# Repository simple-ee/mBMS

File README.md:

# WARNING!
Just a reminder that this is a DIY product/solution so don’t use this for safety 
critical systems or in any situation where there could be a risk to life. 
There is no warranty, it may not work as expected or at all.

# modular BMS by simple-ee.com
This is what I am calling the modular BMS for an 8S LiFePO4 pack.  I've designed
this as three main parts.  Currently this design is functional and running my
system but I am in the progress of overhauling the design by upgrading from an 
8-bit ATmega328PB to a 32-bit SAMD21G18 using the arduino zero bootloader.

Right now I'm essentially maxed out resources and memory on the atmega328PB and
cannot add anymore features which is why I'm planning on upgrading the design.

Even though this design is now my old design its still very functional and very
stable as it has been running my 4kWh system for about 6 months and protecting 
the cells perfectly.  

The reason for making it a modular design is for easy upgradability and also,
considering the current chip shortage, is to replace sections of the board in
case there are no parts available.  This will prevent the need to redo and 
re-layout of the entire design.

I'm posting this design because I've learned a lot from other projects and feel
this will help a lot of people and want to give back.  Also smarter people than
me could take this design and help optomize the code and design and make this a
community BMS.

## the Table of Contents
1. [the Setup](#thesetup)
    1. [Software/Bootloader](#software)
    2. [Wiring and Connection](#connect)
2. [Pinout and Block Diagram](#pinout)
3. [Board Information](#information)
    1. [the Protection Board](#theProtectionBoard)
    2. [the BMS Board](#theBMSBoard)
    3. [the Passive Board](#thePassiveBoard)
    4. [the Display](#display)

## the SETUP 

### Software/Bootloader 
[Software Setup](https://github.com/simple-ee/mBMS/tree/main/Setup)

### Wiring and Connection 
#### Single 8S Pack Wiring Diagram
Here we have the wiring diagram for connecting the mBMS to an 8S pack and is considered a single pack system:

#### Parallel multiple 8S Wiring Diagram
Here we have the wiring diagram for connecting multiple 8S packs in parallel.  Here each 8S pack is protected by its own mBMS and then they are paralleled together using 
ideal diodes to make sure that the other packs in parallel do not charge or discharge a pack that has gone into protection.  I designed the system this way to allow
for scalability of system storage.  By protecting each pack separately then you can, theoretically, add tens of hundreds of 8S packs in parallel when you need more storage
without having to reconfigure your system to add more storage or turn off the system to add more storage.

## Pinout and Block Diagram 

### the Protection Board

## Board information 

### the Protection board 

[kicad Files and gerber files](https://github.com/simple-ee/mBMS/tree/main/Schematic/The%20Protection%20Board)

#### Rendered PCB

#### Actual PCB

- This board will handle discharge and charge currents between the battery
and the external world.  
- It has the following specs:

    Item | Description
    -----|------------
    1 | 4-Channel 16-BIT ADC with an effective resolution of 16-Bit at 20sps
    2 | 100A hall effect current sensor
    3 | Up to 3 Discharge N-Channel MOSFETS with 0.7mOhm DCR and 425A current capability. ( Effective current handling per mosfet without heatsink is 30A)
    4 | Up to 2 charge N-Channle MOSFETS with 0.7mOhm DCR and 425A current capability. (Effective current handling per mosfet without heatsink is 30A)
    5 | Optoisolator to drive the charge mosfets as it is floating relative to the battery ground.
    6 | High efficiency buck converter to power the MCU and supporting circuits.
    7 | Low power LDO to power the secondary side of the optoisolator to drive the charge MOSFET
    8 | Two I2C ports, one to act as an internal COM for adc and display, andsecond one to act as external COM to relay information to BMS board
    9 | 125A fuse that will act as the short circuit protection with a breaking capacity of 1kA.

### the BMS Board 

[kicad Files and gerber files](https://github.com/simple-ee/mBMS/tree/main/Schematic/The%20BMS%20Board)

#### Rendered PCB

#### Actual PCB

- This board is handling the cell level monitoring function as well as sending
controls to the passive balance resistors for balancing the cells.  It 
incorporates cell level OVP and UVP which is configurable and also receives the
current values from the Protection board via I2C and then displays all values
on a TFT display either ST7735 or ST7789.  If for any reason a fault is triggered
or one of the configured protection values is triggered you can send a reset
fault command either via an external trigger button or serial command over uart.
- It has the following specs:

Item | Description
-----|------------
1 | x2 4-Channel 16-BIT ADC with an effective resolution of 16-BIT at 20sps
2 | External 16MHz Crystal oscillator
3 | External SPI port to connect TFT display
4 | Can be powered via the battery pack or external power source
5 | External action button. Default state is for reset fault condition

### the Passive Balance Board 

[kicad Files and gerber files](https://github.com/simple-ee/mBMS/tree/main/Schematic/The%20Passive%20Balance%20Board)

#### Rendered PCB

#### Actual PCB

The passive board essentially is controlled by the BMS board to allow the 
bleeder resistor to slow down the rate of charge for that particular cell when
the BMS board detects that the cell is too high of a delta from the rest.

Currently I have a 2W 10R resistor but I'm having thermal issues because its 
quite a lot of power to dissapate over the whole board so I'd recommend a 22R 2W
resistor which is still good for what you need but will not cause any potential
damage.

The board also have the option of adding thermal jumpers and if you do decide to 
do that then I'd recommend a 2oz copper for that PCB.  Thermal jumpers are electrically
isolated and allow you to connect directly to ground without shorting anything
which is pretty awesome in my opinion.

Heres the link for the thermal jumpers.  They are really awesome but with the chip
shortage its a decent lead time for them.

https://www.digikey.com/en/products/detail/vishay-dale-thin-film/THJP0612AST1/11313314

### the Display (optional) 

Currently the SoC is not an implemented function its just a placeholder.  But if
anyone is willing to help out with this SoC code section then that would be 
awesome as I'm still not sure the best way to implement this.

The screen is to be used with the BMS board.  the Protection does not have 
the ability to use a SPI TFT display but if you use it on its own, then you can
add an I2C oled display because the secondary I2C will not be used.

Here is a link to the tft display that I used.
https://www.adafruit.com/product/4383

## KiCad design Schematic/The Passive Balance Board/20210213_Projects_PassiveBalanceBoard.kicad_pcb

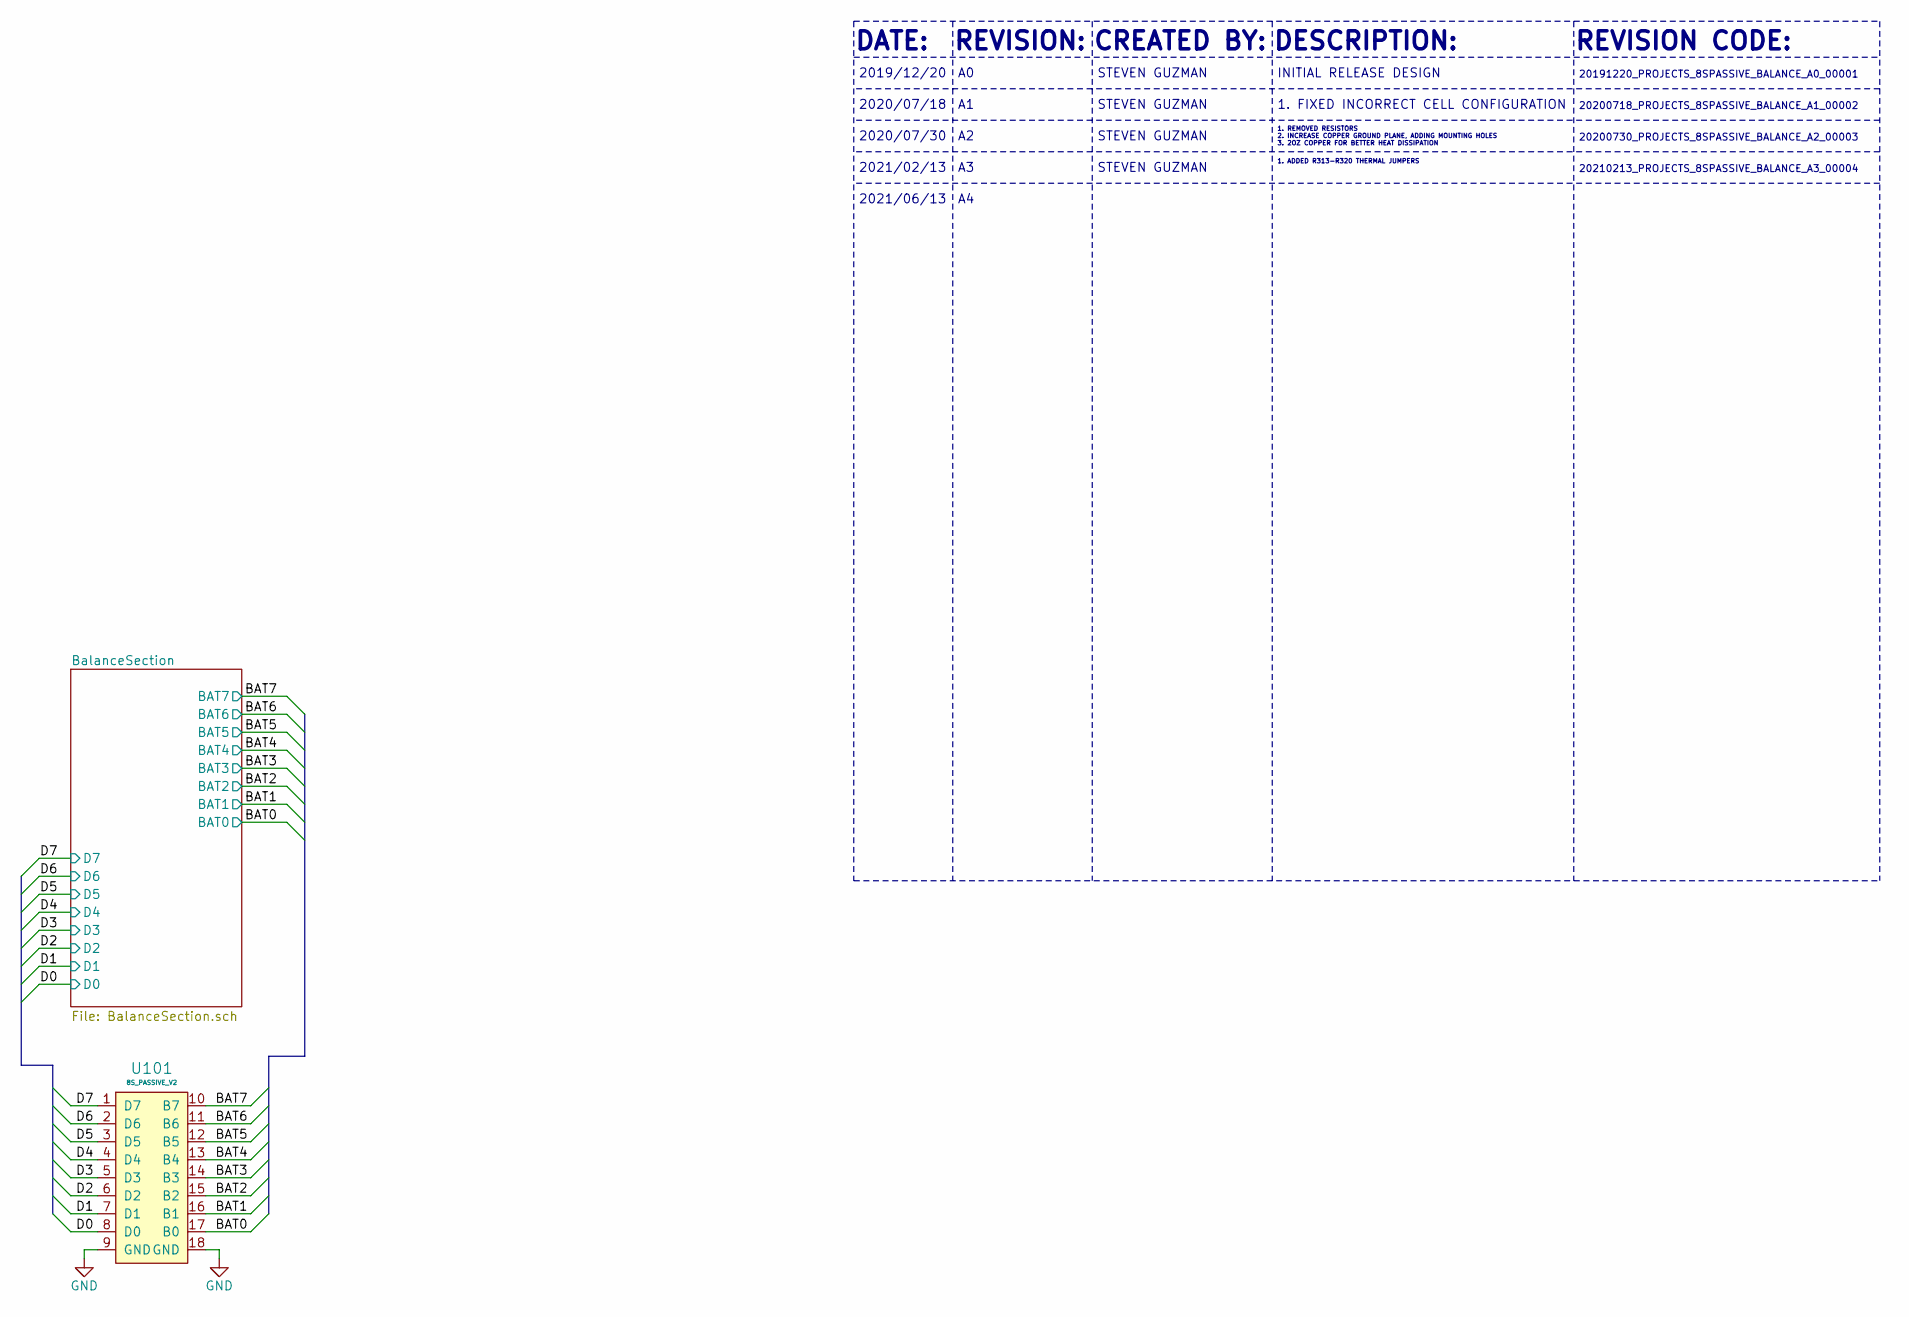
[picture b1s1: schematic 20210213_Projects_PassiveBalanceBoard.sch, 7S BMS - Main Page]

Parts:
U101: 8S_PASSIVE_V2

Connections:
/BAT0: U101.17 (B0); also elsewhere on the board
/BAT1: U101.16 (B1); also elsewhere on the board
/BAT2: U101.15 (B2); also elsewhere on the board
/BAT3: U101.14 (B3); also elsewhere on the board
/BAT4: U101.13 (B4); also elsewhere on the board
/BAT5: U101.12 (B5); also elsewhere on the board
/BAT6: U101.11 (B6); also elsewhere on the board
/BAT7: U101.10 (B7); also elsewhere on the board
/D0: U101.8 (D0); also elsewhere on the board
/D1: U101.7 (D1); also elsewhere on the board
/D2: U101.6 (D2); also elsewhere on the board
/D3: U101.5 (D3); also elsewhere on the board
/D4: U101.4 (D4); also elsewhere on the board
/D5: U101.3 (D5); also elsewhere on the board
/D6: U101.2 (D6); also elsewhere on the board
/D7: U101.1 (D7); also elsewhere on the board
GND: U101.9 (GND), U101.18 (GND); also elsewhere on the board

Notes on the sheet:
DATE:
DESCRIPTION:
REVISION:
REVISION CODE:
2019/12/20
CREATED BY:
STEVEN GUZMAN
INITIAL RELEASE DESIGN
20191220_PROJECTS_8SPASSIVE_BALANCE_A0_00001
2020/07/18
1. FIXED INCORRECT CELL CONFIGURATION
20200718_PROJECTS_8SPASSIVE_BALANCE_A1_00002
2020/07/30
1. REMOVED RESISTORS 2. INCREASE COPPER GROUND PLANE, ADDING MOUNTING HOLES 3. 2OZ COPPER FOR BETTER HEAT DISSIPATION
20200730_PROJECTS_8SPASSIVE_BALANCE_A2_00003
2021/02/13
1. ADDED R313-R320 THERMAL JUMPERS
20210213_PROJECTS_8SPASSIVE_BALANCE_A3_00004
2021/06/13

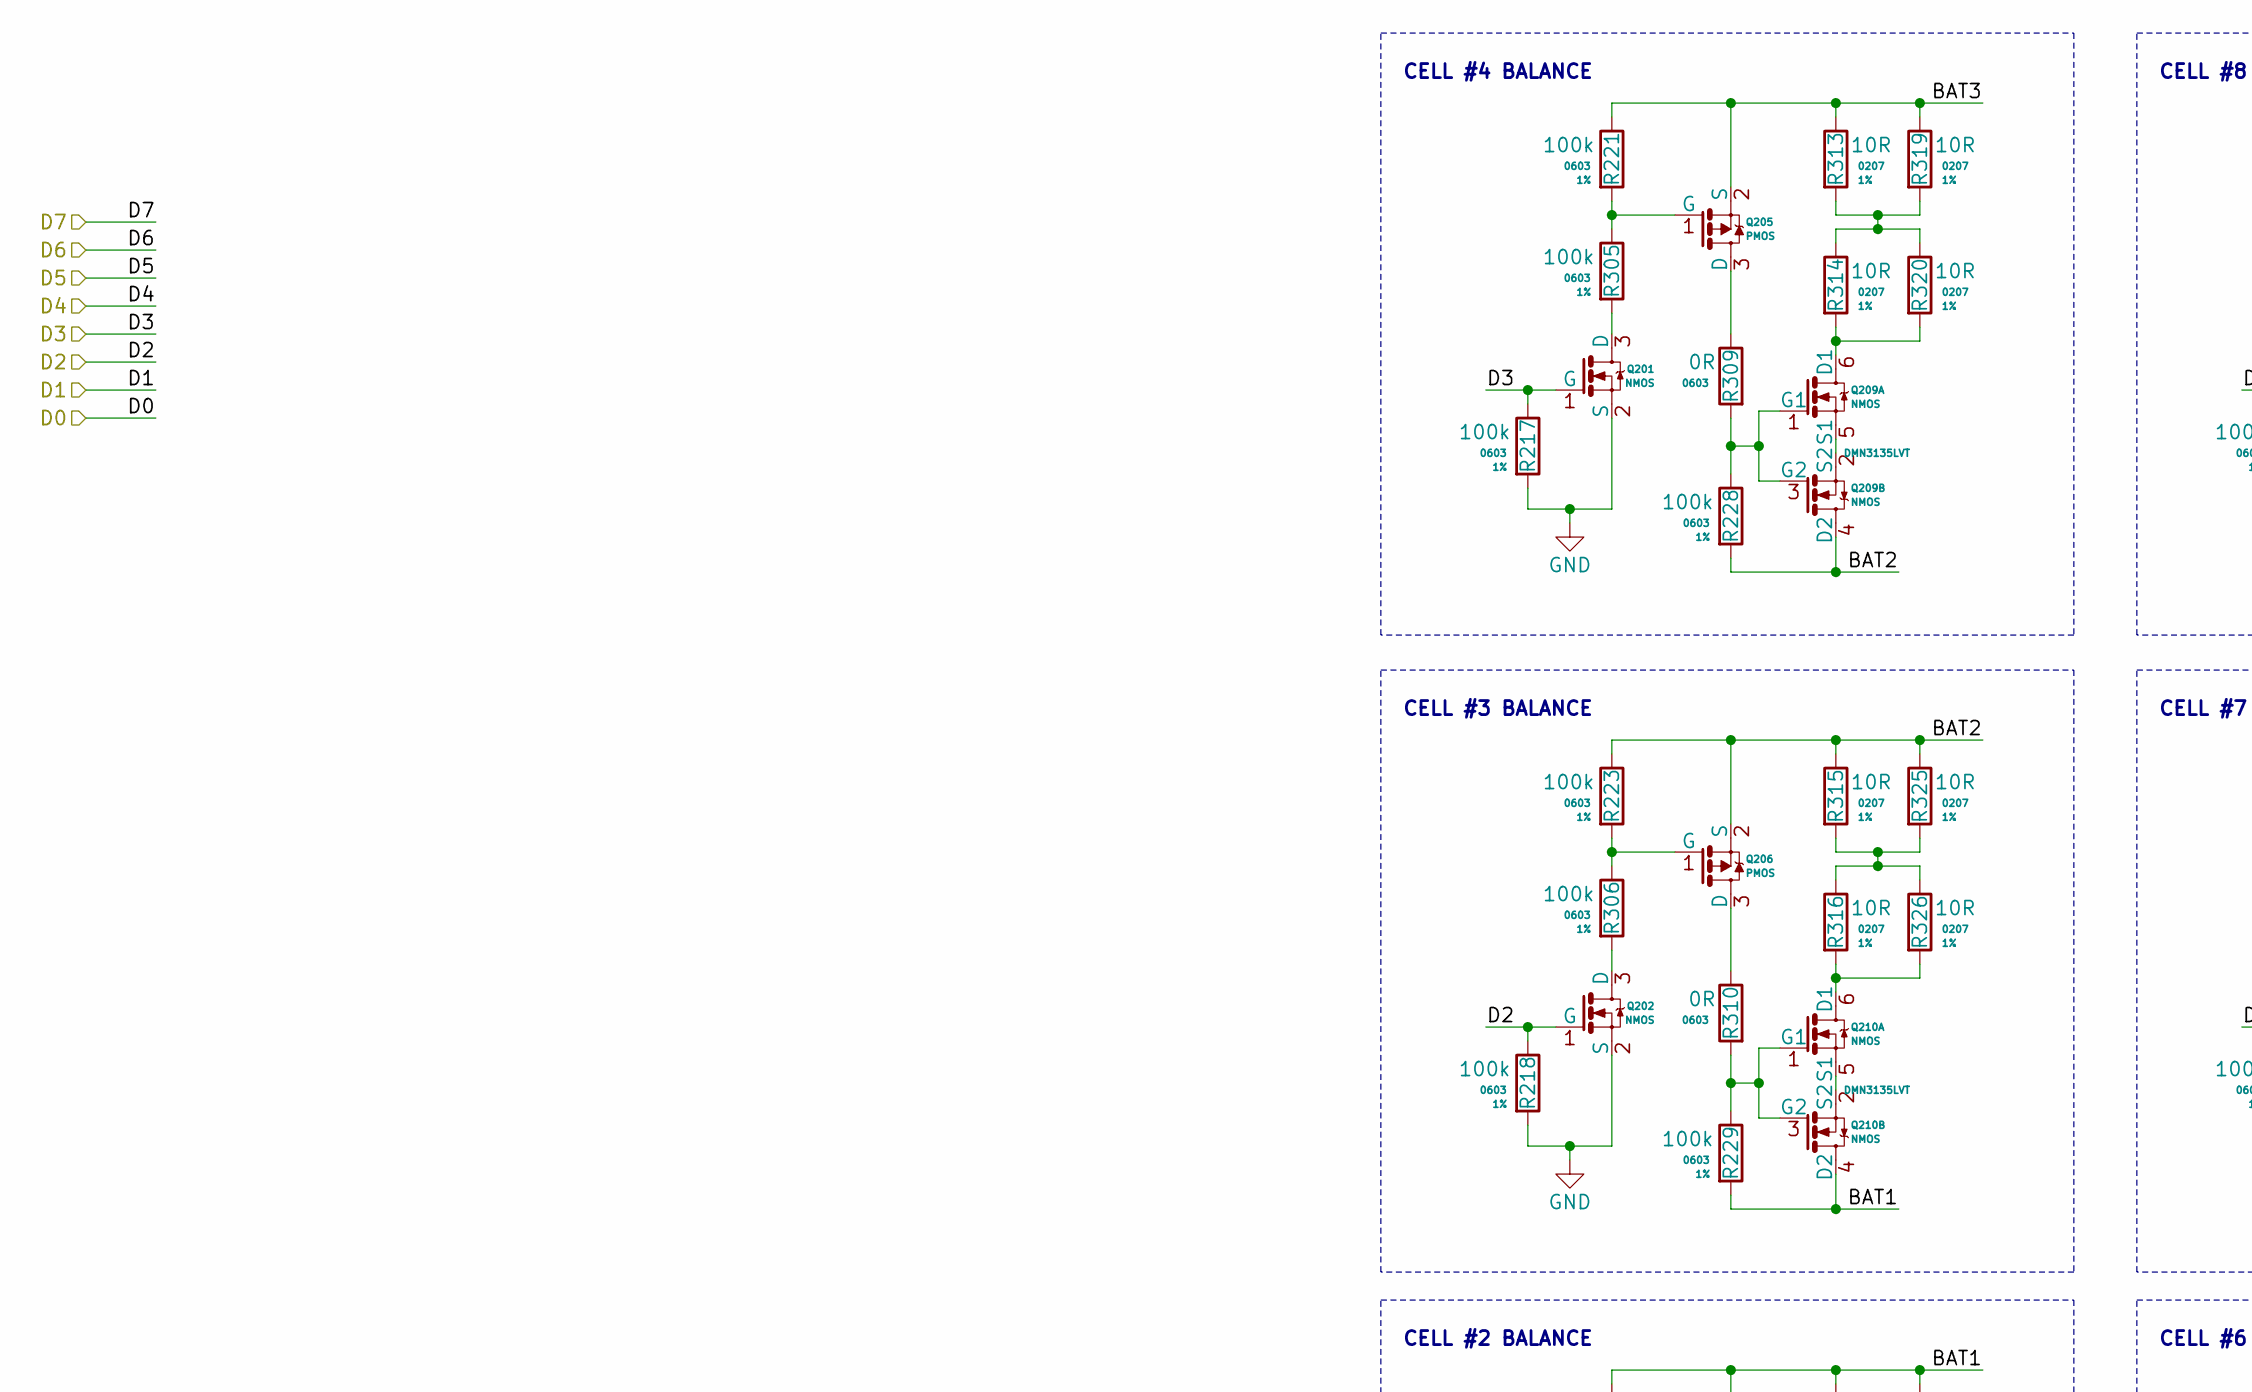
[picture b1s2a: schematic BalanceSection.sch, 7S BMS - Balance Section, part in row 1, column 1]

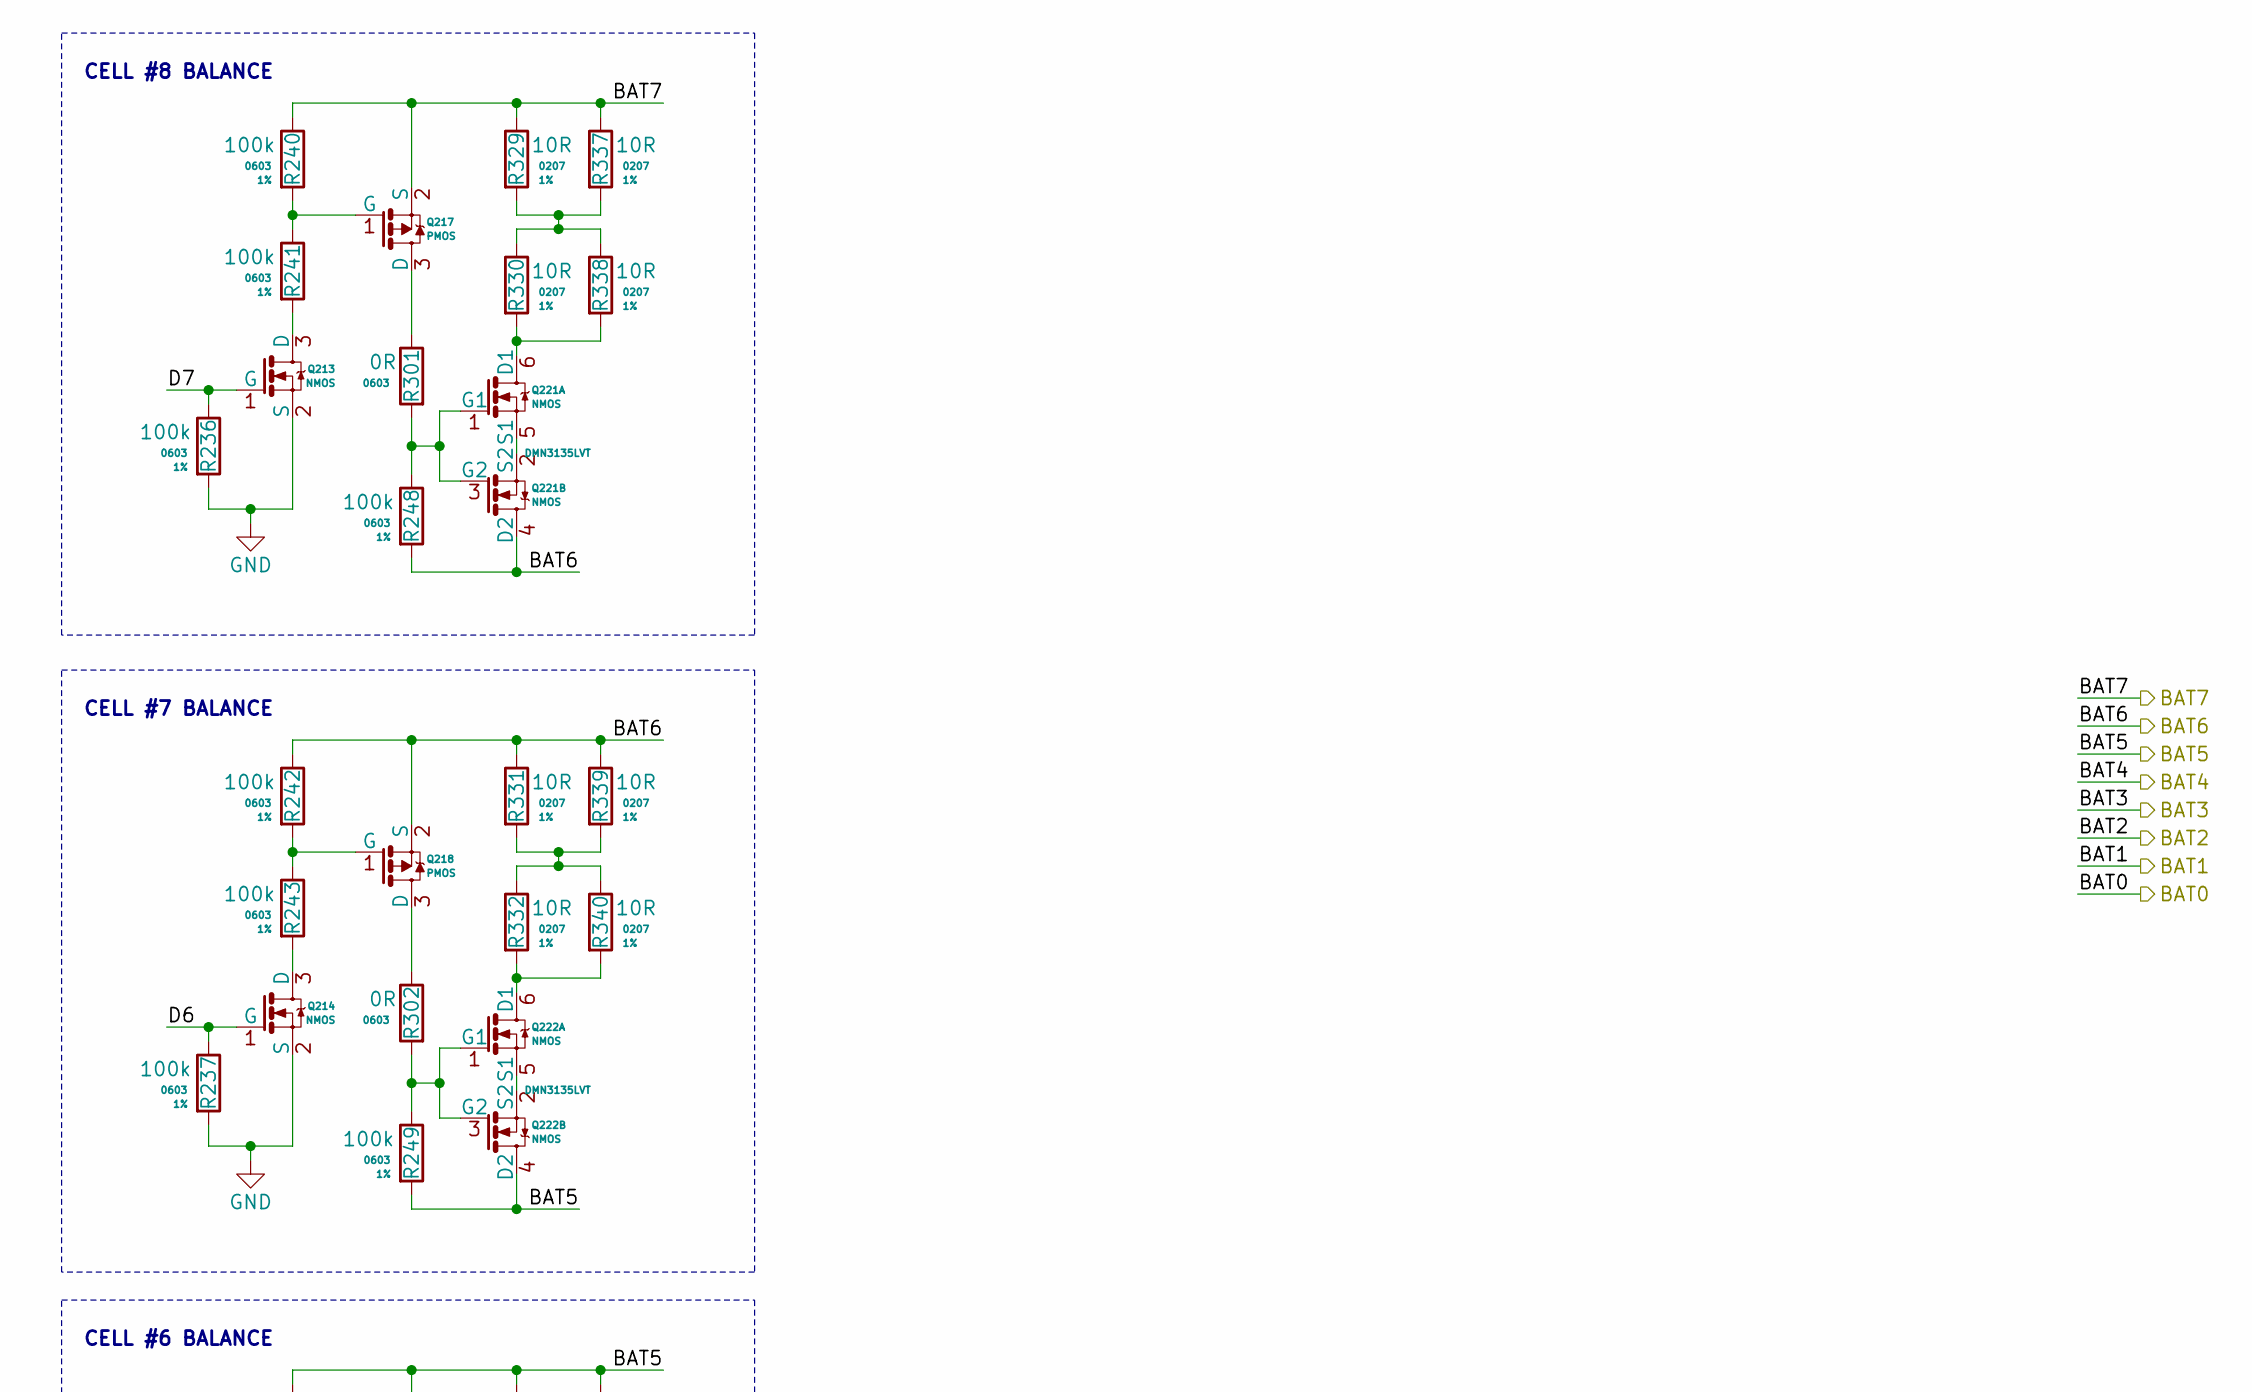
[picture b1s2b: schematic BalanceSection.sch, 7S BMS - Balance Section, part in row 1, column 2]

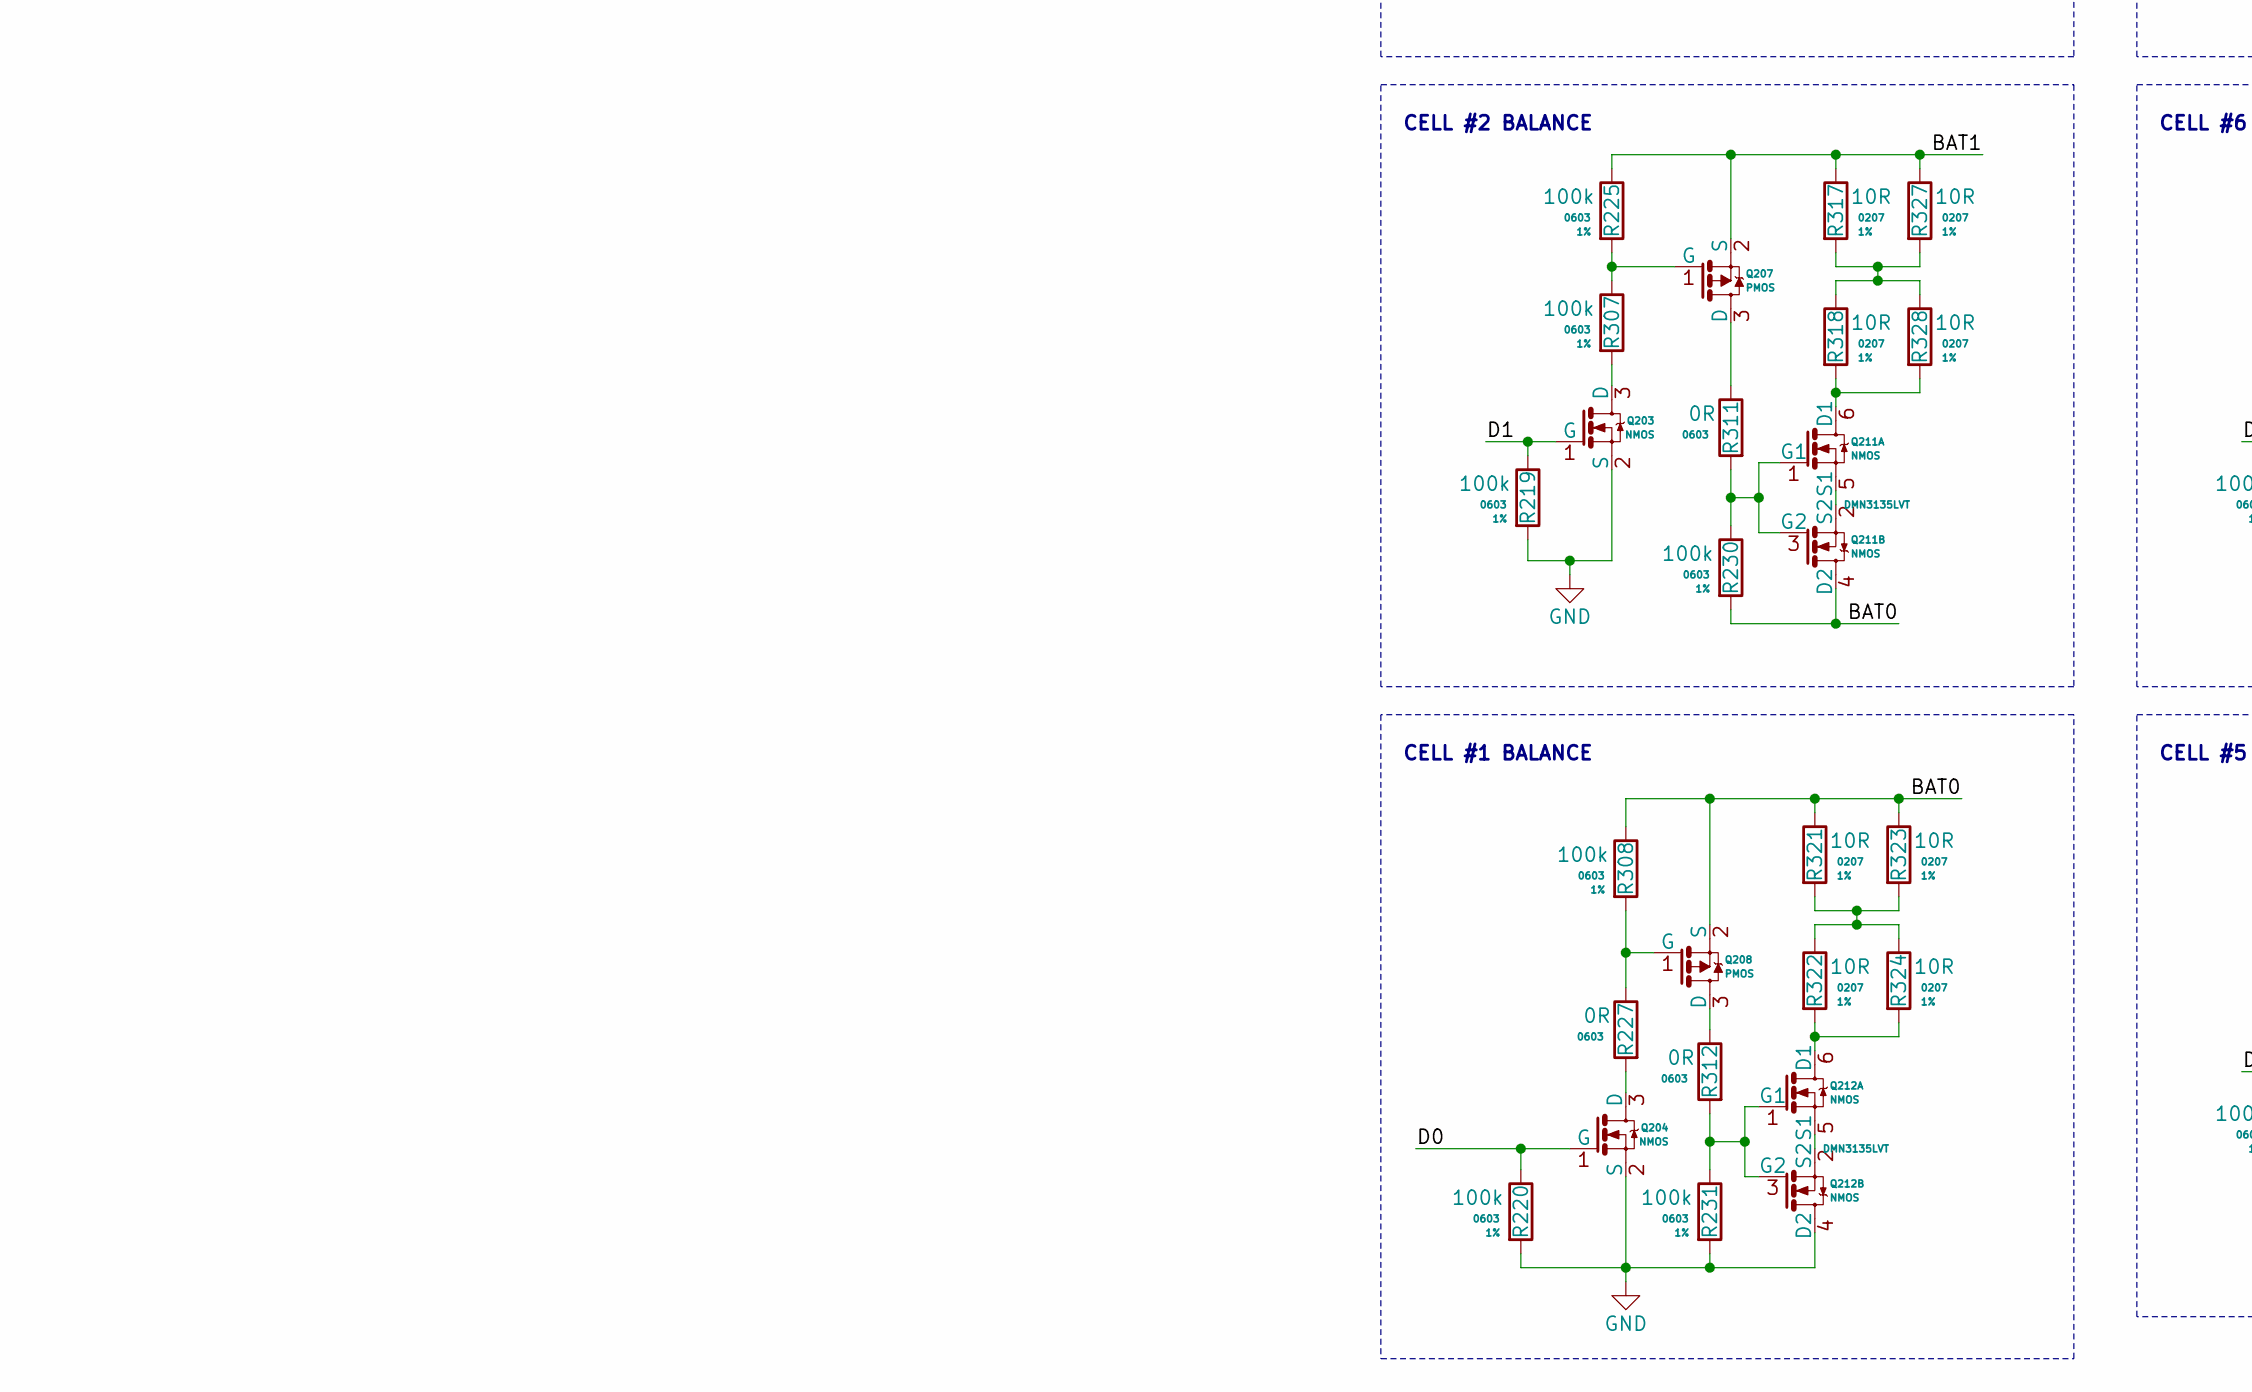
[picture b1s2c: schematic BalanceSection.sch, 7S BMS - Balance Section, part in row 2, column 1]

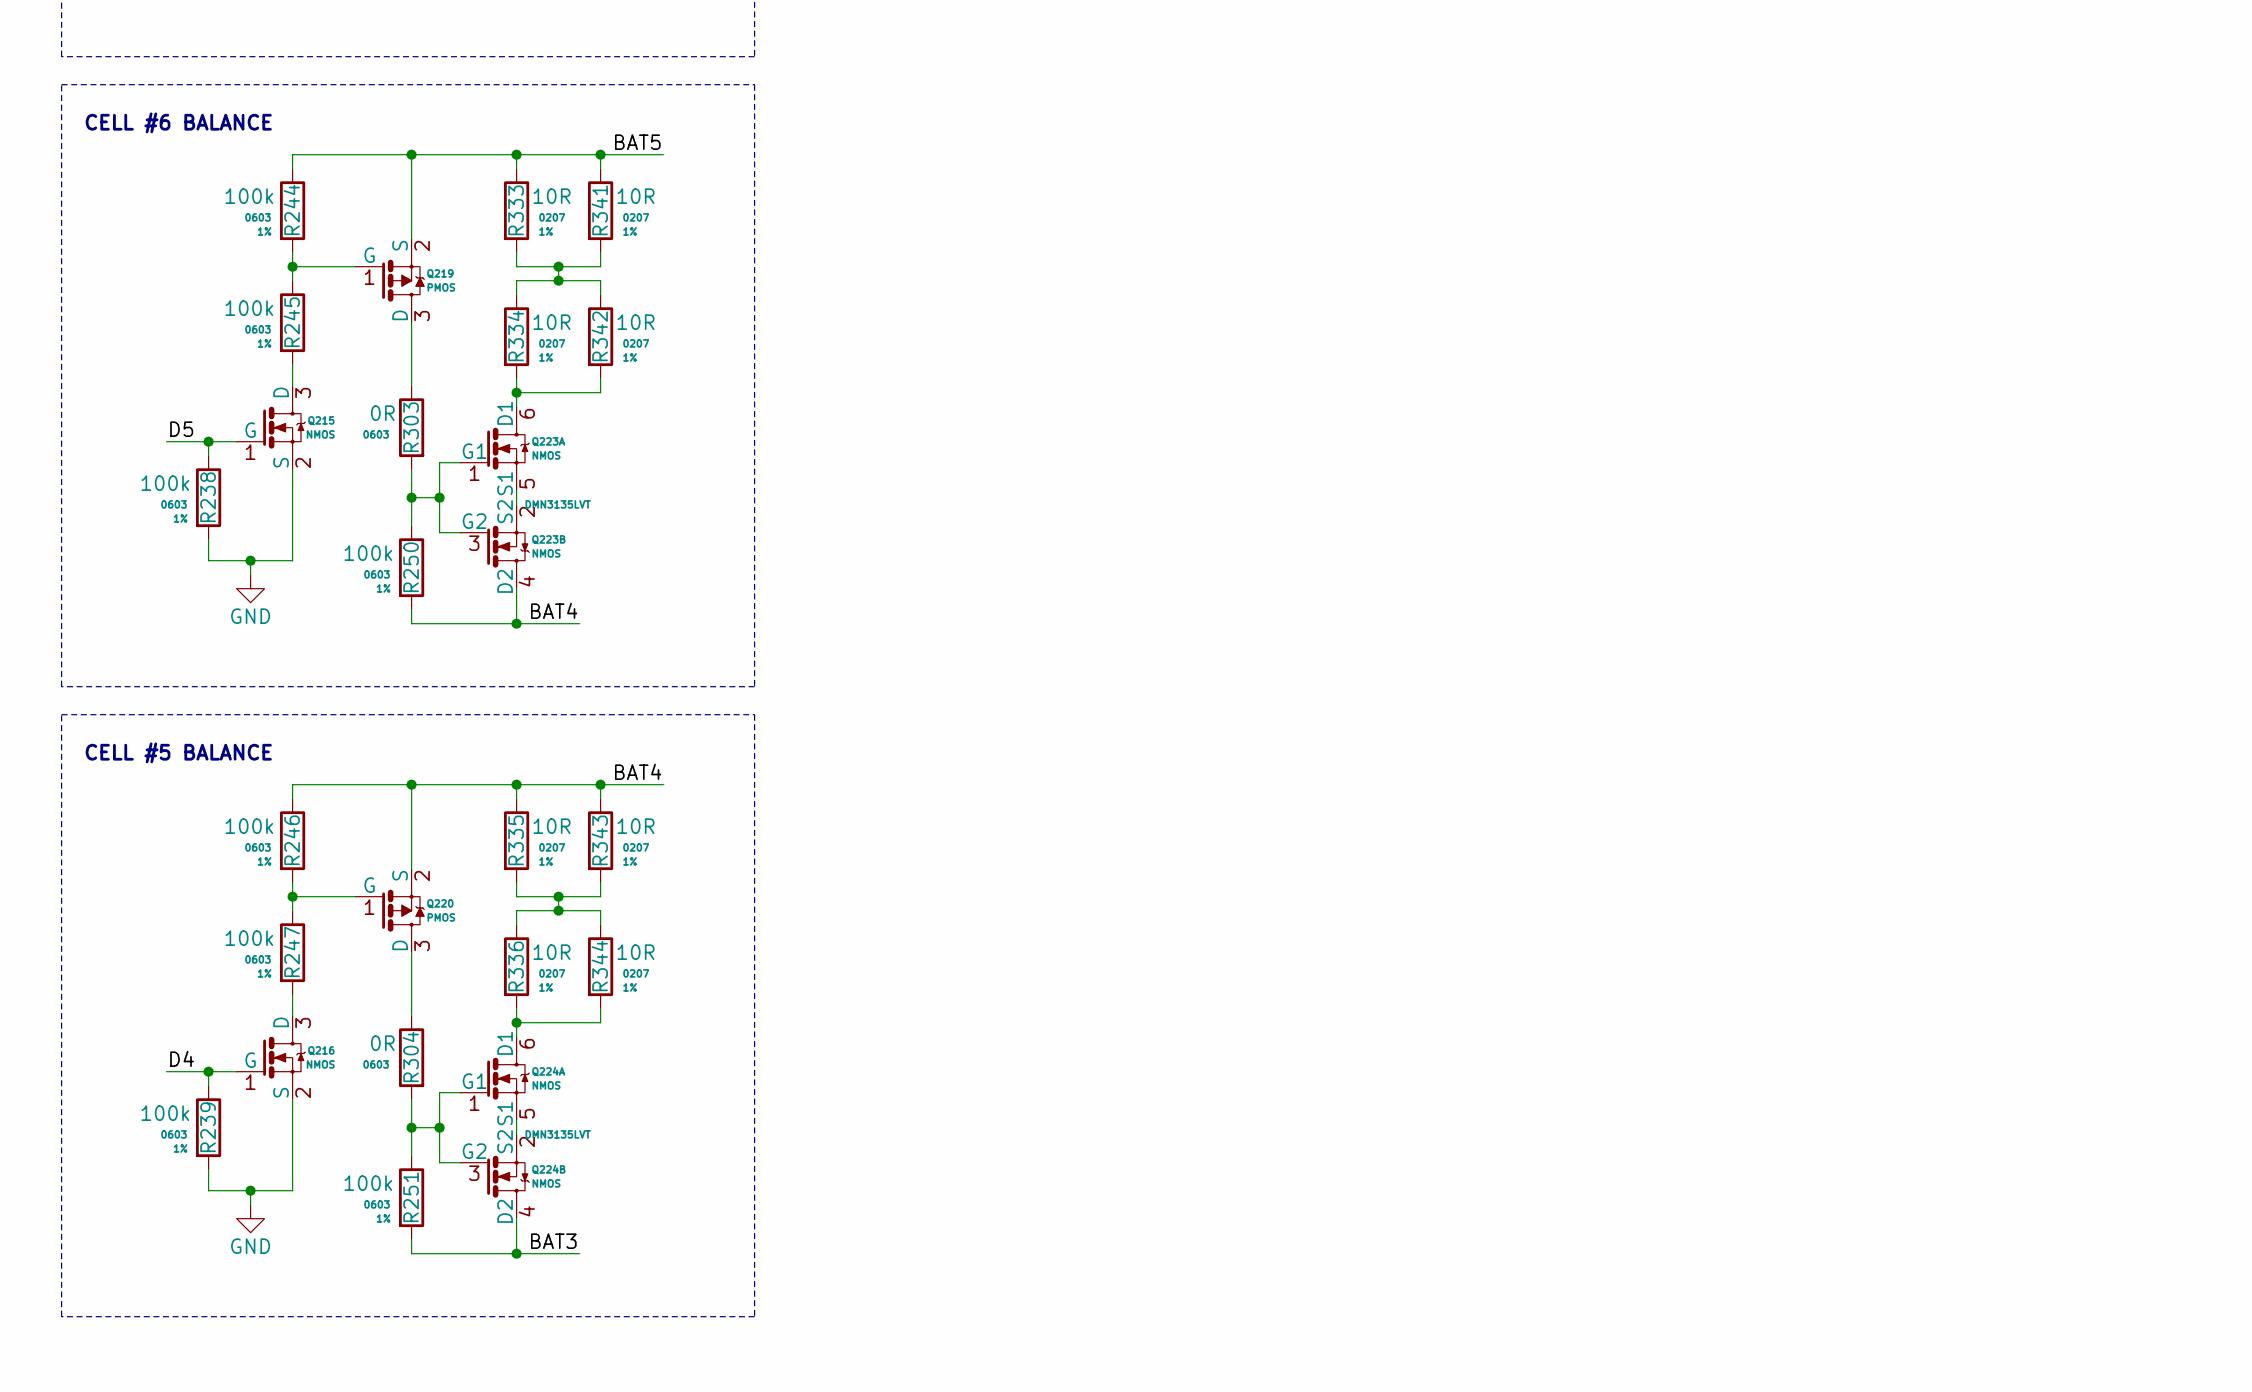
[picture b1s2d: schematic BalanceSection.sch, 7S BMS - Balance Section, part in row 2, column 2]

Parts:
Q201, Q202, Q203, Q204, Q213, Q214, Q215, Q216: 2N7002-7-F; SOT-23-3
Q205, Q206, Q207, Q208, Q217, Q218, Q219, Q220: BSS84LT1G; SOT-23-3
Q209, Q210, Q211, Q212, Q221, Q222, Q223, Q224: DMN3135LVT; SOT-23-6
R217, R218, R219, R220, R221, R223, R225, R228, R229, R230, R231, R236, R237, R238, R239, R240, R241, R242, R243, R244, R245, R246, R247, R248, R249, R250, R251, R305, R306, R307, R308: CPF0603F100KC1; R_0603_Handsolder
R227, R301, R302, R303, R304, R309, R310, R311, R312: RMCF0603ZT0R00; R_0603_Handsolder
R313, R314, R315, R316, R317, R318, R319, R320, R321, R322, R323, R324, R325, R326, R327, R328, R329, R330, R331, R332, R333, R334, R335, R336, R337, R338, R339, R340, R341, R342, R343, R344: MLFA1FTC10R0; R_MELF_0207

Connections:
/BAT0: Q208.2 (S), Q211.4 (D2), R230.2, R308.1, R321.1, R323.1; also elsewhere on the board
/BAT1: Q207.2 (S), Q210.4 (D2), R225.1, R229.2, R317.1, R327.1; also elsewhere on the board
/BAT2: Q206.2 (S), Q209.4 (D2), R223.1, R228.2, R315.1, R325.1; also elsewhere on the board
/BAT3: Q205.2 (S), Q224.4 (D2), R221.1, R251.2, R313.1, R319.1; also elsewhere on the board
/BAT4: Q220.2 (S), Q223.4 (D2), R246.1, R250.2, R335.1, R343.1; also elsewhere on the board
/BAT5: Q219.2 (S), Q222.4 (D2), R244.1, R249.2, R333.1, R341.1; also elsewhere on the board
/BAT6: Q218.2 (S), Q221.4 (D2), R242.1, R248.2, R331.1, R339.1; also elsewhere on the board
/BAT7: Q217.2 (S), R240.1, R329.1, R337.1; also elsewhere on the board
/D0: Q204.1 (G), R220.1; also elsewhere on the board
/D1: Q203.1 (G), R219.1; also elsewhere on the board
/D2: Q202.1 (G), R218.1; also elsewhere on the board
/D3: Q201.1 (G), R217.1; also elsewhere on the board
/D4: Q216.1 (G), R239.1; also elsewhere on the board
/D5: Q215.1 (G), R238.1; also elsewhere on the board
/D6: Q214.1 (G), R237.1; also elsewhere on the board
/D7: Q213.1 (G), R236.1; also elsewhere on the board
GND: Q201.2 (S), Q202.2 (S), Q203.2 (S), Q204.2 (S), Q212.4 (D2), Q213.2 (S), Q214.2 (S), Q215.2 (S), Q216.2 (S), R217.2, R218.2, R219.2, R220.2, R231.2, R236.2, R237.2, R238.2, R239.2; also elsewhere on the board
unnamed: Q201.3 (D), R305.2
unnamed: Q202.3 (D), R306.2
unnamed: Q203.3 (D), R307.2
unnamed: Q204.3 (D), R227.2
unnamed: Q205.1 (G), R221.2, R305.1
unnamed: Q205.3 (D), R309.1
unnamed: Q206.1 (G), R223.2, R306.1
unnamed: Q206.3 (D), R310.1
unnamed: Q207.1 (G), R225.2, R307.1
unnamed: Q207.3 (D), R311.1
unnamed: Q208.1 (G), R227.1, R308.2
unnamed: Q208.3 (D), R312.1
unnamed: Q209.1 (G1), Q209.3 (G2), R228.1, R309.2
unnamed: Q209.2 (S2), Q209.5 (S1)
unnamed: Q209.6 (D1), R314.2, R320.2
unnamed: Q210.1 (G1), Q210.3 (G2), R229.1, R310.2
unnamed: Q210.2 (S2), Q210.5 (S1)
unnamed: Q210.6 (D1), R316.2, R326.2
unnamed: Q211.1 (G1), Q211.3 (G2), R230.1, R311.2
unnamed: Q211.2 (S2), Q211.5 (S1)
unnamed: Q211.6 (D1), R318.2, R328.2
unnamed: Q212.1 (G1), Q212.3 (G2), R231.1, R312.2
unnamed: Q212.2 (S2), Q212.5 (S1)
unnamed: Q212.6 (D1), R322.2, R324.2
unnamed: Q213.3 (D), R241.2
unnamed: Q214.3 (D), R243.2
unnamed: Q215.3 (D), R245.2
unnamed: Q216.3 (D), R247.2
unnamed: Q217.1 (G), R240.2, R241.1
unnamed: Q217.3 (D), R301.1
unnamed: Q218.1 (G), R242.2, R243.1
unnamed: Q218.3 (D), R302.1
unnamed: Q219.1 (G), R244.2, R245.1
unnamed: Q219.3 (D), R303.1
unnamed: Q220.1 (G), R246.2, R247.1
unnamed: Q220.3 (D), R304.1
unnamed: Q221.1 (G1), Q221.3 (G2), R248.1, R301.2
unnamed: Q221.2 (S2), Q221.5 (S1)
unnamed: Q221.6 (D1), R330.2, R338.2
unnamed: Q222.1 (G1), Q222.3 (G2), R249.1, R302.2
unnamed: Q222.2 (S2), Q222.5 (S1)
unnamed: Q222.6 (D1), R332.2, R340.2
unnamed: Q223.1 (G1), Q223.3 (G2), R250.1, R303.2
unnamed: Q223.2 (S2), Q223.5 (S1)
unnamed: Q223.6 (D1), R334.2, R342.2
unnamed: Q224.1 (G1), Q224.3 (G2), R251.1, R304.2
unnamed: Q224.2 (S2), Q224.5 (S1)
unnamed: Q224.6 (D1), R336.2, R344.2
unnamed: R313.2, R314.1, R319.2, R320.1
unnamed: R315.2, R316.1, R325.2, R326.1
unnamed: R317.2, R318.1, R327.2, R328.1
unnamed: R321.2, R322.1, R323.2, R324.1
unnamed: R329.2, R330.1, R337.2, R338.1
unnamed: R331.2, R332.1, R339.2, R340.1
unnamed: R333.2, R334.1, R341.2, R342.1
unnamed: R335.2, R336.1, R343.2, R344.1

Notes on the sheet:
CELL #1 BALANCE
CELL #2 BALANCE
CELL #3 BALANCE
CELL #4 BALANCE
CELL #5 BALANCE
CELL #6 BALANCE
CELL #7 BALANCE
CELL #8 BALANCE

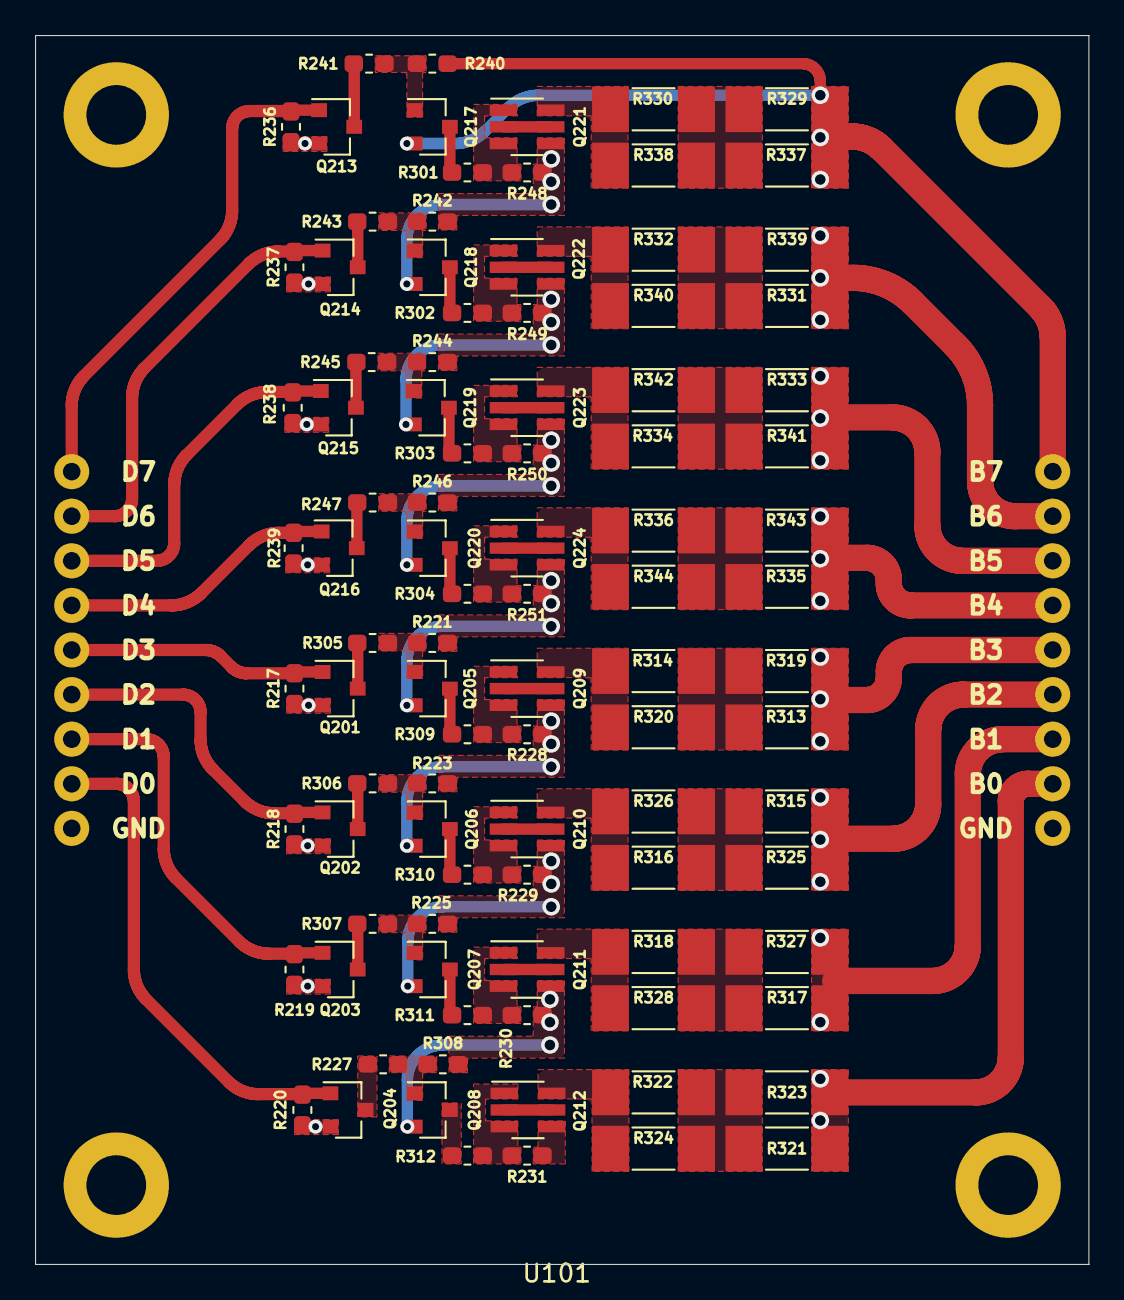
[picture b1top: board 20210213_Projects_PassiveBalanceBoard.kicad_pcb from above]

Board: 2 copper layers, 60.0 x 70.0 mm, 97 parts (0 on the bottom side), 73 nets.

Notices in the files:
parts and their libraries:
Copyright 2016 Accelerated Designs. All rights reserved.
